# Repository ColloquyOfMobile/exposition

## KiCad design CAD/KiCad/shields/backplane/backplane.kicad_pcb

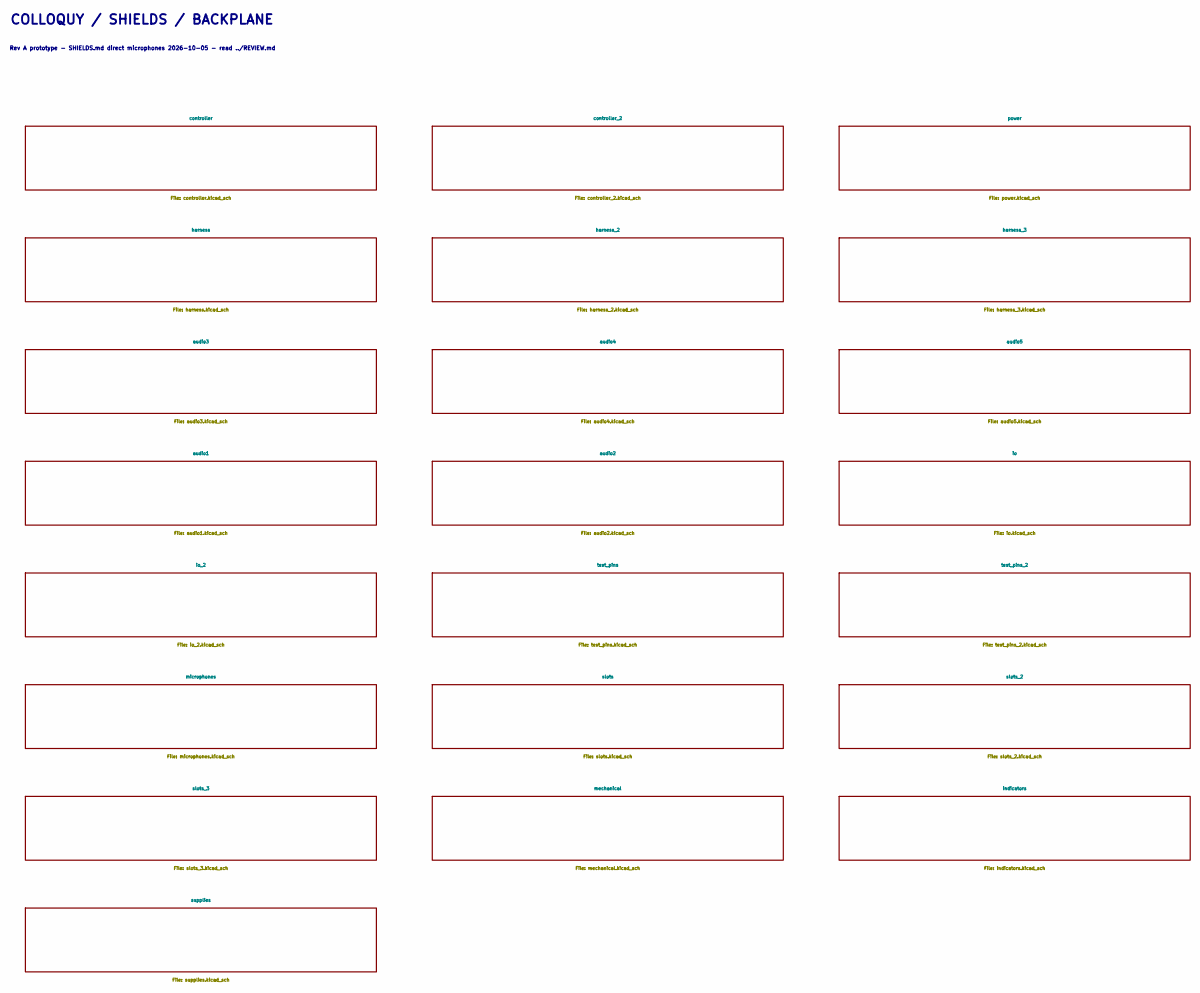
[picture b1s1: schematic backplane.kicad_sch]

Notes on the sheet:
COLLOQUY / SHIELDS / BACKPLANE
Rev A prototype - SHIELDS.md direct microphones 2026-10-05 - read ../REVIEW.md

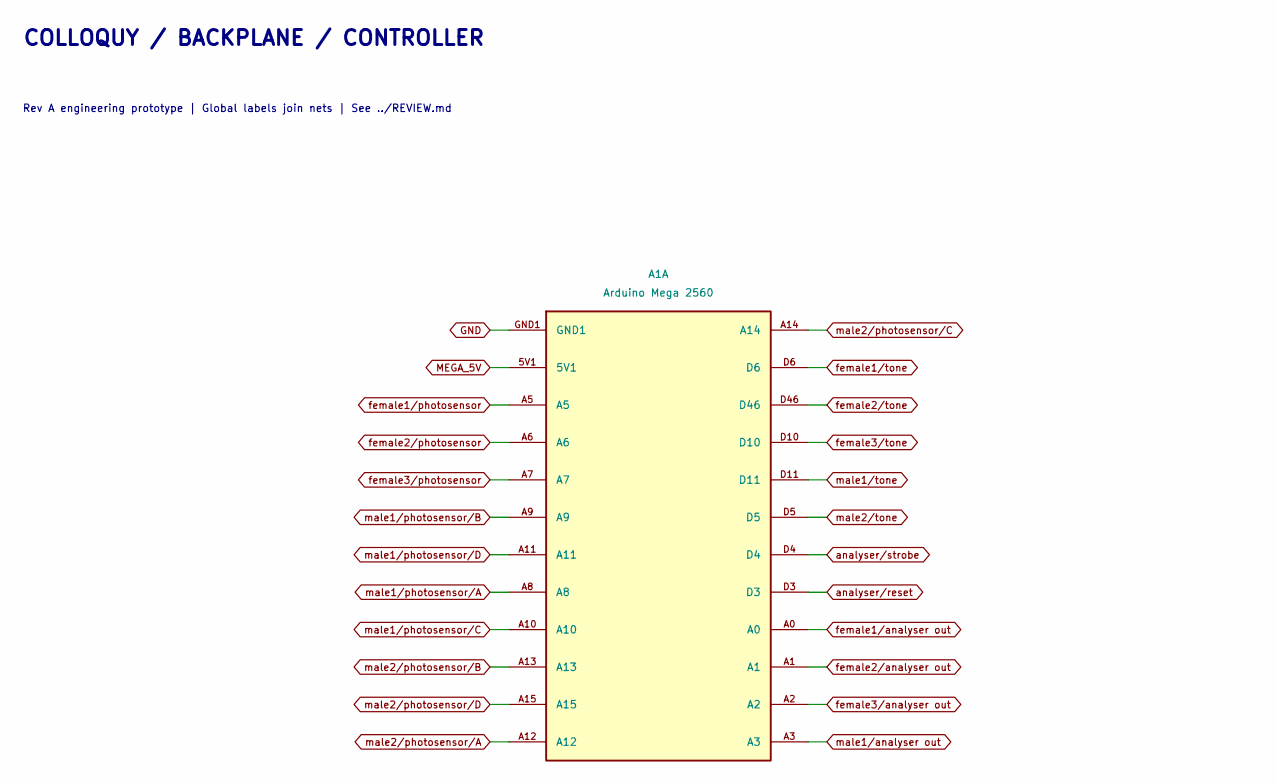
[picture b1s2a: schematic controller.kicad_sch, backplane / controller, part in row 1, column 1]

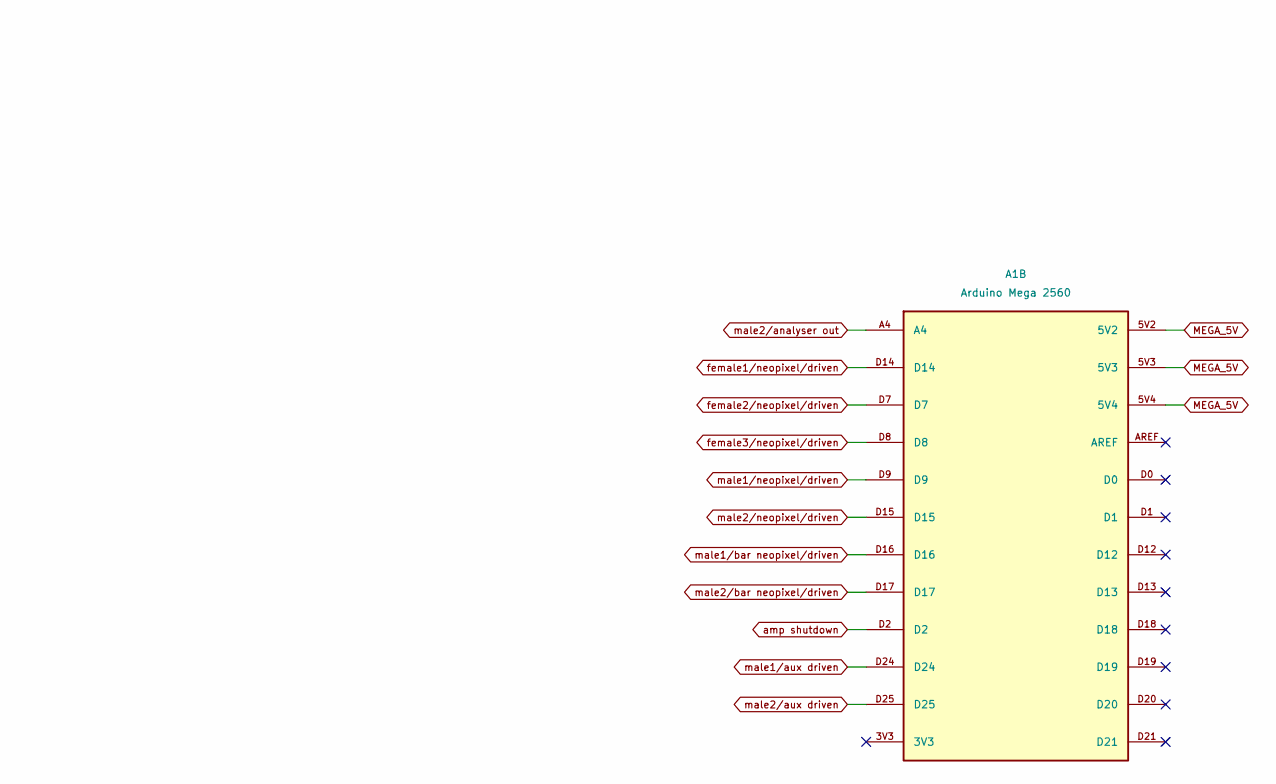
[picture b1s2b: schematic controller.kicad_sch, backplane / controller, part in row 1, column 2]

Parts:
A1: Arduino Mega 2560; Arduino_Mega2560_R3_Shield

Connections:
GND: A1.GND1; also elsewhere on the board
MEGA_5V: A1.5V1, A1.5V2, A1.5V3, A1.5V4; also elsewhere on the board
amp shutdown: A1.D2; also elsewhere on the board
analyser/reset: A1.D3; also elsewhere on the board
analyser/strobe: A1.D4; also elsewhere on the board
female1/analyser out: A1.A0; also elsewhere on the board
female1/neopixel/driven: A1.D14; also elsewhere on the board
female1/photosensor: A1.A5; also elsewhere on the board
female1/tone: A1.D6; also elsewhere on the board
female2/analyser out: A1.A1; also elsewhere on the board
female2/neopixel/driven: A1.D7; also elsewhere on the board
female2/photosensor: A1.A6; also elsewhere on the board
female2/tone: A1.D46; also elsewhere on the board
female3/analyser out: A1.A2; also elsewhere on the board
female3/neopixel/driven: A1.D8; also elsewhere on the board
female3/photosensor: A1.A7; also elsewhere on the board
female3/tone: A1.D10; also elsewhere on the board
male1/analyser out: A1.A3; also elsewhere on the board
male1/aux driven: A1.D24; also elsewhere on the board
male1/bar neopixel/driven: A1.D16; also elsewhere on the board
male1/neopixel/driven: A1.D9; also elsewhere on the board
male1/photosensor/A: A1.A8; also elsewhere on the board
male1/photosensor/B: A1.A9; also elsewhere on the board
male1/photosensor/C: A1.A10; also elsewhere on the board
male1/photosensor/D: A1.A11; also elsewhere on the board
male1/tone: A1.D11; also elsewhere on the board
male2/analyser out: A1.A4; also elsewhere on the board
male2/aux driven: A1.D25; also elsewhere on the board
male2/bar neopixel/driven: A1.D17; also elsewhere on the board
male2/neopixel/driven: A1.D15; also elsewhere on the board
male2/photosensor/A: A1.A12; also elsewhere on the board
male2/photosensor/B: A1.A13; also elsewhere on the board
male2/photosensor/C: A1.A14; also elsewhere on the board
male2/photosensor/D: A1.A15; also elsewhere on the board
male2/tone: A1.D5; also elsewhere on the board

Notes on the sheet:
COLLOQUY / BACKPLANE / CONTROLLER
Rev A engineering prototype | Global labels join nets | See ../REVIEW.md

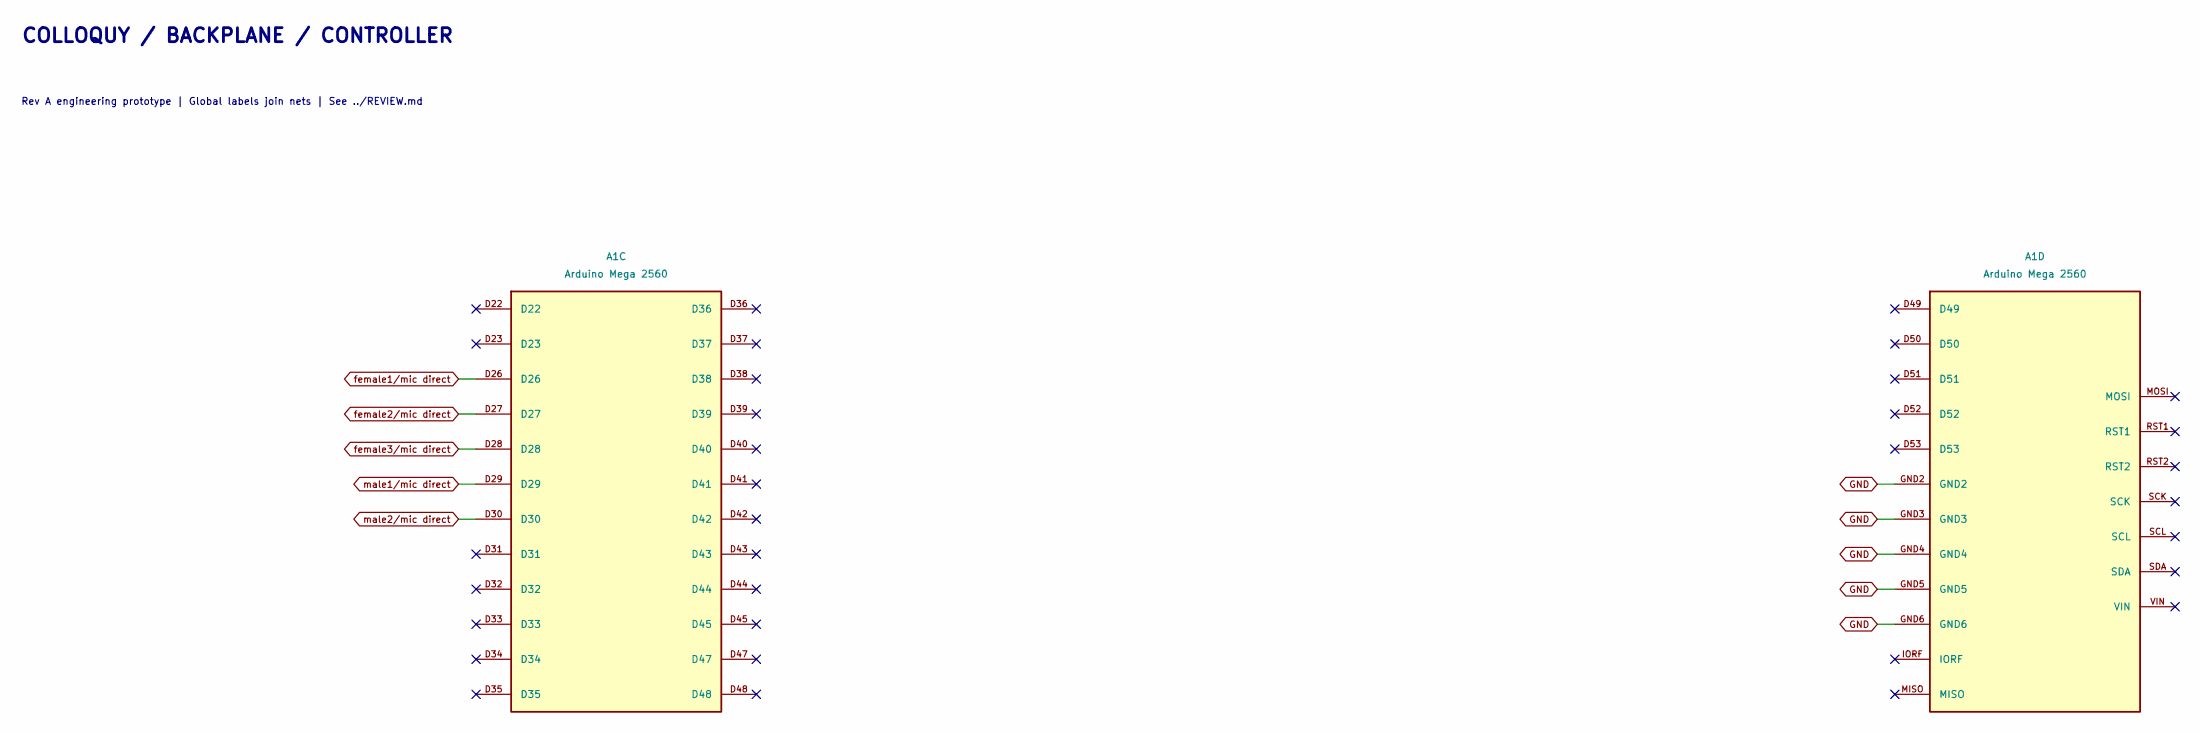
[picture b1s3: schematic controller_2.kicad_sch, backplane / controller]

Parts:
A1: Arduino Mega 2560; Mega_Front_Mirrored

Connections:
GND: A1.GND2, A1.GND3, A1.GND4, A1.GND5, A1.GND6; also elsewhere on the board
female1/mic direct: A1.D26; also elsewhere on the board
female2/mic direct: A1.D27; also elsewhere on the board
female3/mic direct: A1.D28; also elsewhere on the board
male1/mic direct: A1.D29; also elsewhere on the board
male2/mic direct: A1.D30; also elsewhere on the board

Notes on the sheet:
COLLOQUY / BACKPLANE / CONTROLLER
Rev A engineering prototype | Global labels join nets | See ../REVIEW.md

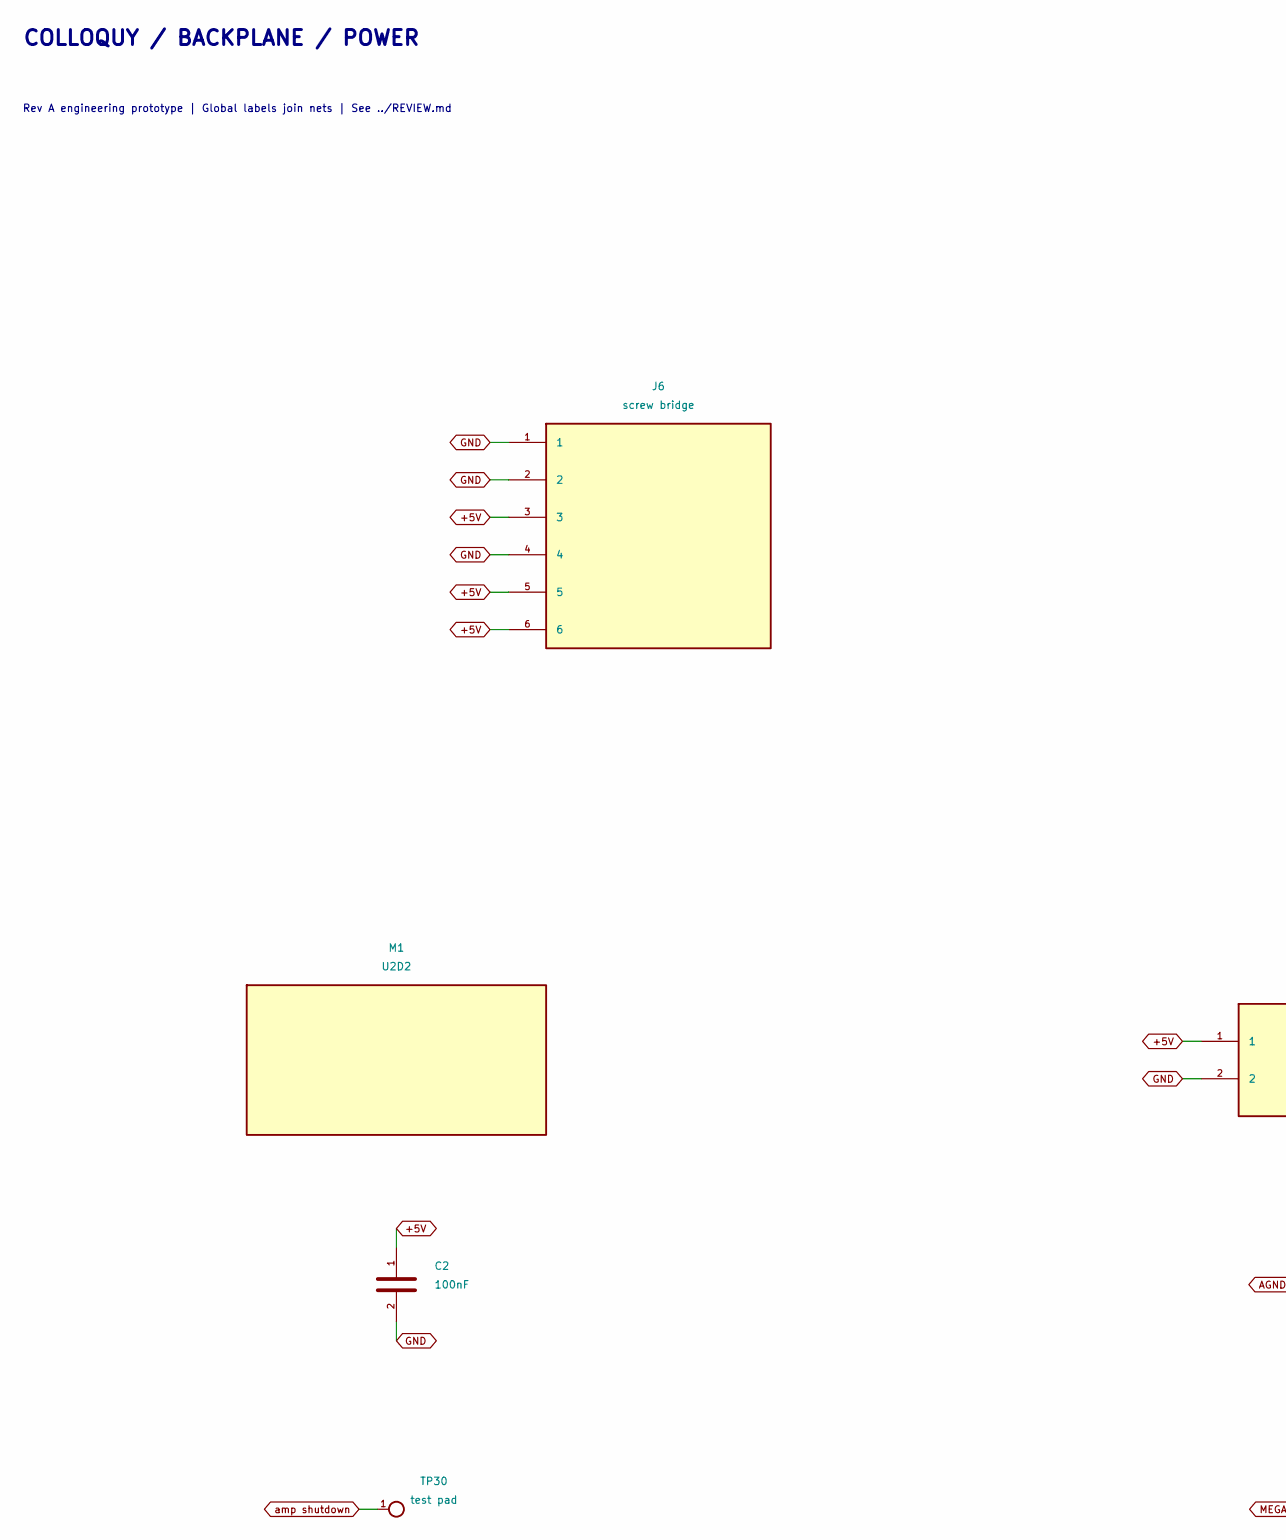
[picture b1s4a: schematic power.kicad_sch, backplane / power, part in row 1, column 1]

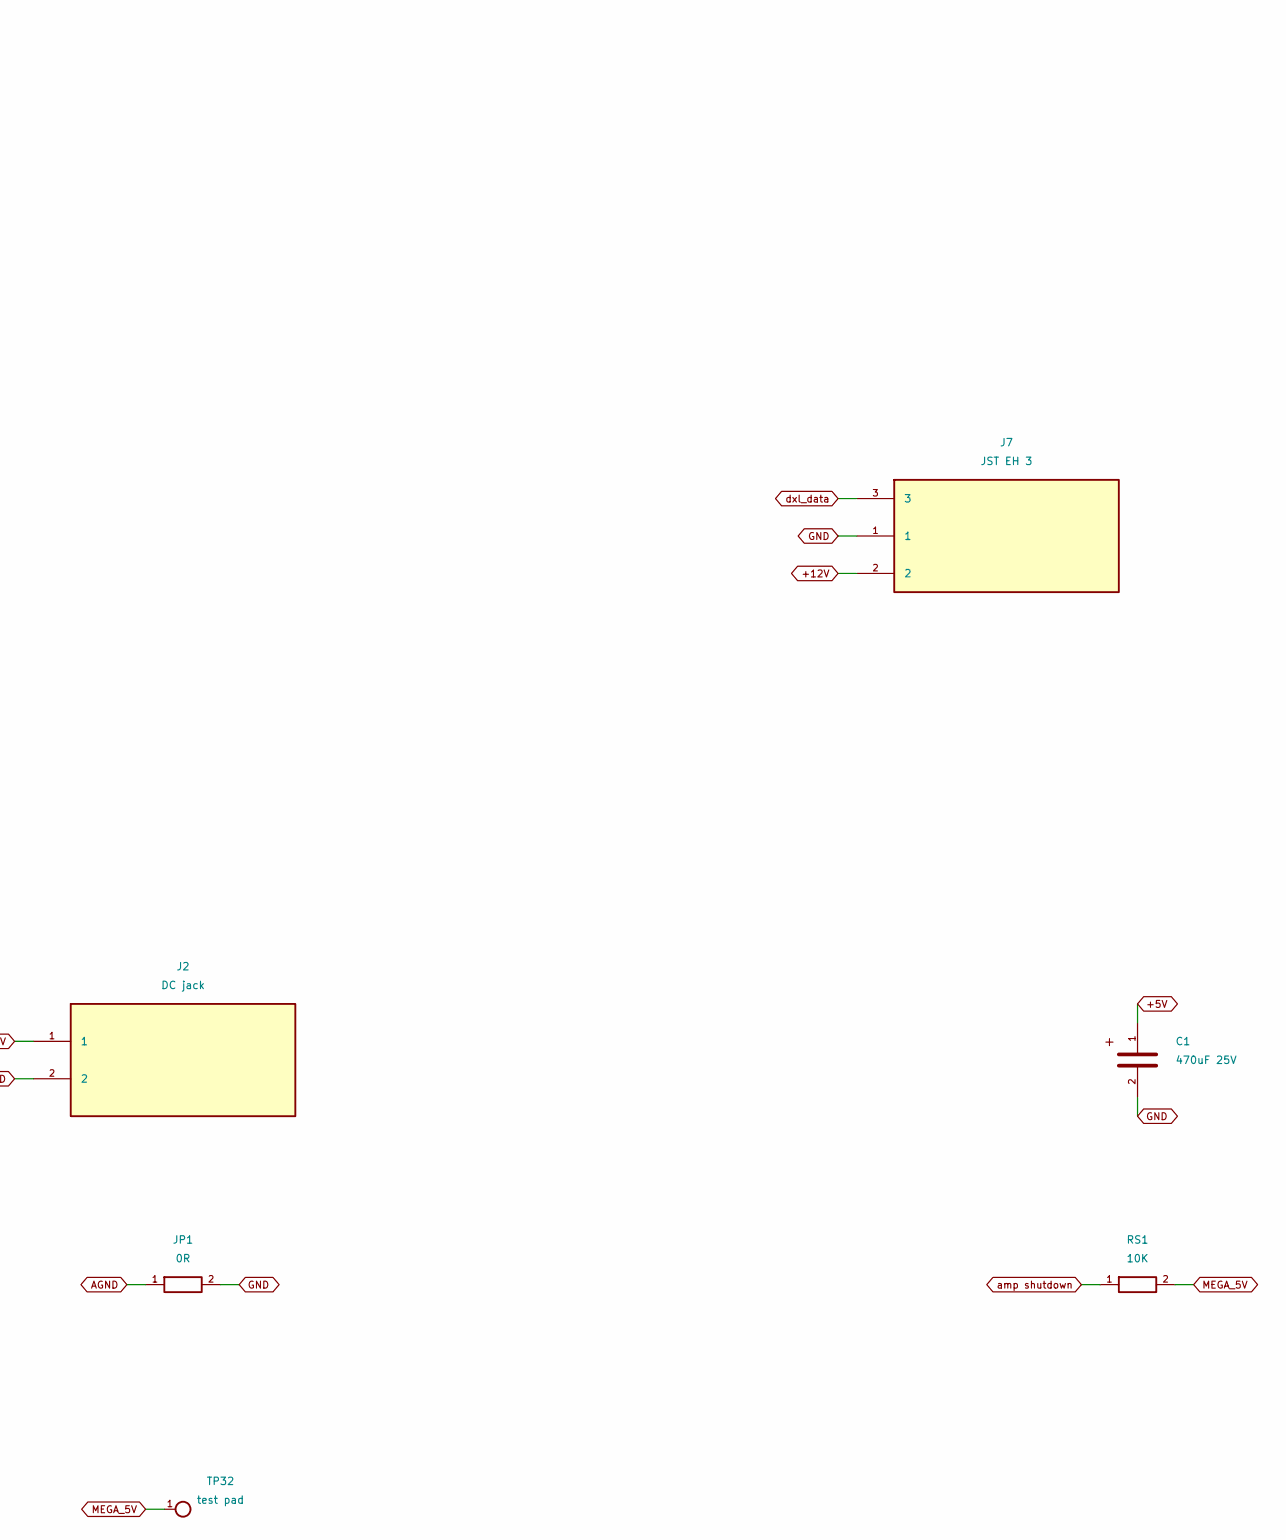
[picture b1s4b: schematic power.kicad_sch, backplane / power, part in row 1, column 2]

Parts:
C1: 470uF 25V; CP_Elec_10x10.5
C2: 100nF; C_0603_1608Metric
J2: DC jack; PJ-082BH_jack_10A
J6: screw bridge; screw_brigde
J7: JST EH 3; JST_EH_B3B-EH-A_1x03_P2.50mm_Vertical
JP1: 0R; R_0805_2012Metric
M1: U2D2; u2d2_mounting
RS1: 10K; R_0603_1608Metric
TP30, TP32: test pad; TestPoint_Pad_D1.5mm

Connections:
+5V: C1.1, C2.1, J2.1, J6.3, J6.5, J6.6; also elsewhere on the board
+12V: J7.2; also elsewhere on the board
AGND: JP1.1; also elsewhere on the board
GND: C1.2, C2.2, J2.2, J6.1, J6.2, J6.4, J7.1, JP1.2; also elsewhere on the board
MEGA_5V: RS1.2, TP32.1; also elsewhere on the board
amp shutdown: RS1.1, TP30.1; also elsewhere on the board
dxl_data: J7.3; also elsewhere on the board

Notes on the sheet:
COLLOQUY / BACKPLANE / POWER
Rev A engineering prototype | Global labels join nets | See ../REVIEW.md

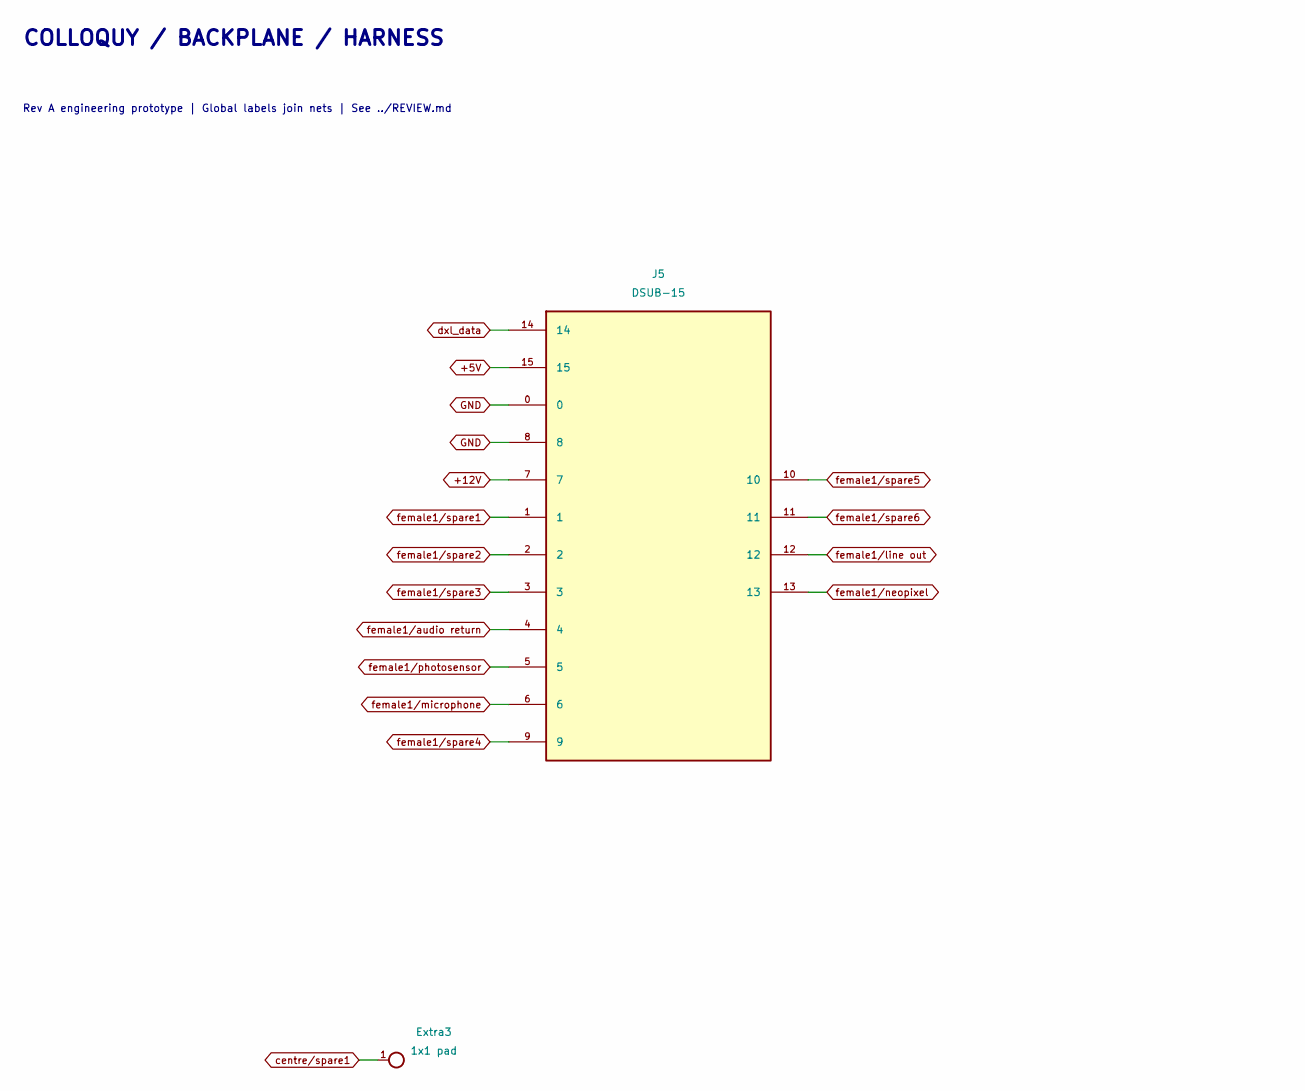
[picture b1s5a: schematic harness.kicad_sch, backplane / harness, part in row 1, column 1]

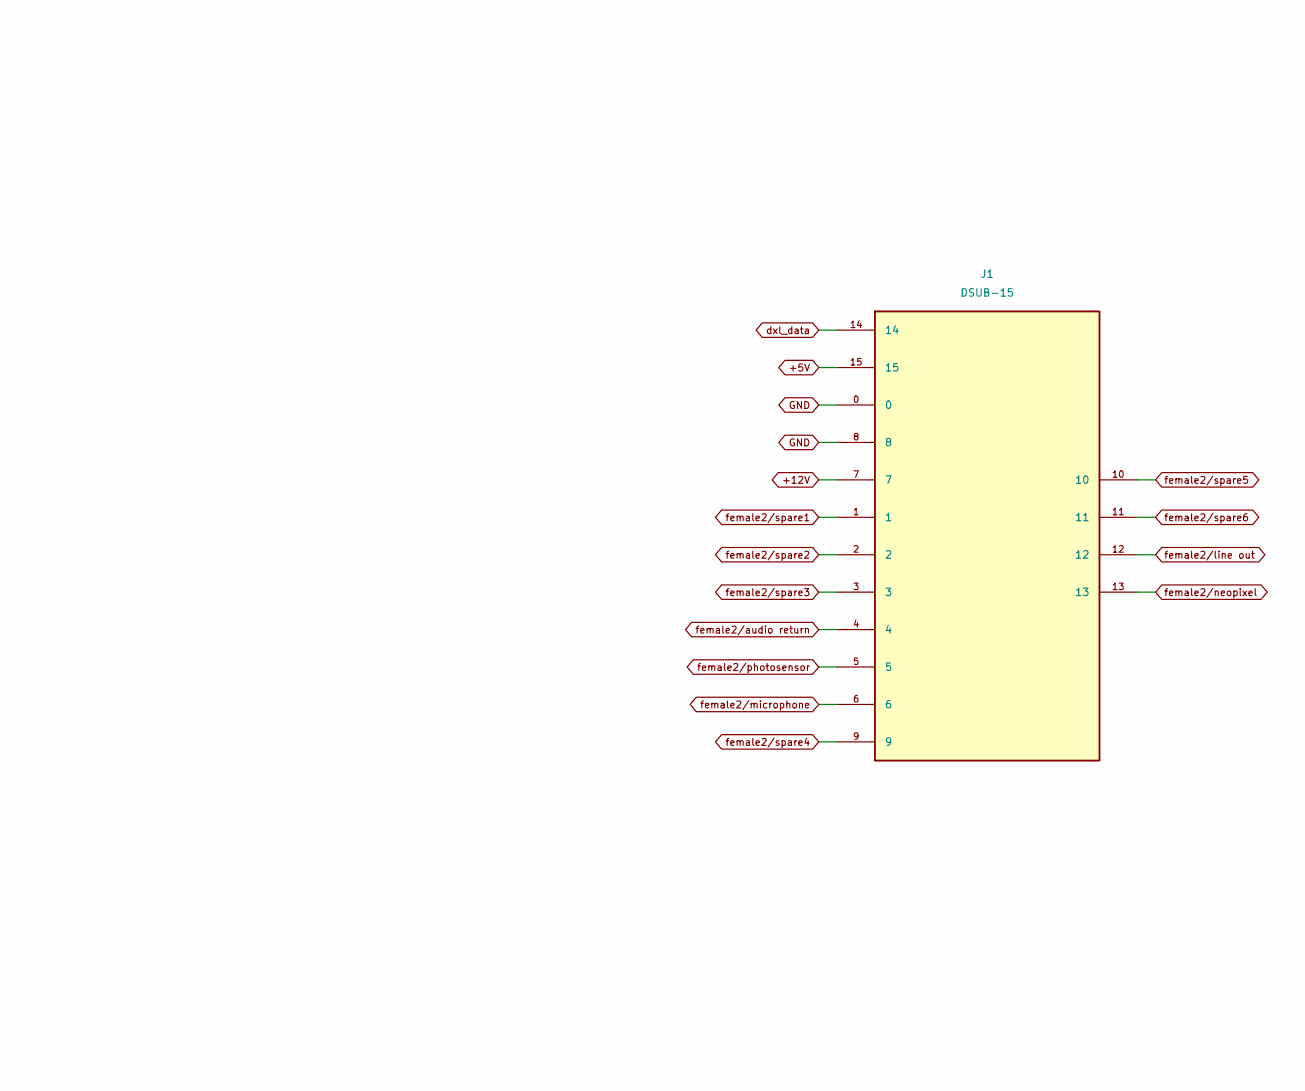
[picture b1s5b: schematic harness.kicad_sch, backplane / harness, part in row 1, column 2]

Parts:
Extra3: 1x1 pad; PinHeader_1x01_P2.54mm_Vertical
J1, J5: DSUB-15; DSUB-15_Pins_Horizontal_P2.77x2.84mm_EdgePinOffset4.94mm_Ho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

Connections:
+5V: J1.15, J5.15; also elsewhere on the board
+12V: J1.7, J5.7; also elsewhere on the board
GND: J1.0, J1.8, J5.0, J5.8; also elsewhere on the board
centre/spare1: Extra3.1; also elsewhere on the board
dxl_data: J1.14, J5.14; also elsewhere on the board
female1/audio return: J5.4; also elsewhere on the board
female1/line out: J5.12; also elsewhere on the board
female1/microphone: J5.6; also elsewhere on the board
female1/neopixel: J5.13; also elsewhere on the board
female1/photosensor: J5.5; also elsewhere on the board
female1/spare1: J5.1; also elsewhere on the board
female1/spare2: J5.2; also elsewhere on the board
female1/spare3: J5.3; also elsewhere on the board
female1/spare4: J5.9; also elsewhere on the board
female1/spare5: J5.10; also elsewhere on the board
female1/spare6: J5.11; also elsewhere on the board
female2/audio return: J1.4; also elsewhere on the board
female2/line out: J1.12; also elsewhere on the board
female2/microphone: J1.6; also elsewhere on the board
female2/neopixel: J1.13; also elsewhere on the board
female2/photosensor: J1.5; also elsewhere on the board
female2/spare1: J1.1; also elsewhere on the board
female2/spare2: J1.2; also elsewhere on the board
female2/spare3: J1.3; also elsewhere on the board
female2/spare4: J1.9; also elsewhere on the board
female2/spare5: J1.10; also elsewhere on the board
female2/spare6: J1.11; also elsewhere on the board

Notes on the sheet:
COLLOQUY / BACKPLANE / HARNESS
Rev A engineering prototype | Global labels join nets | See ../REVIEW.md

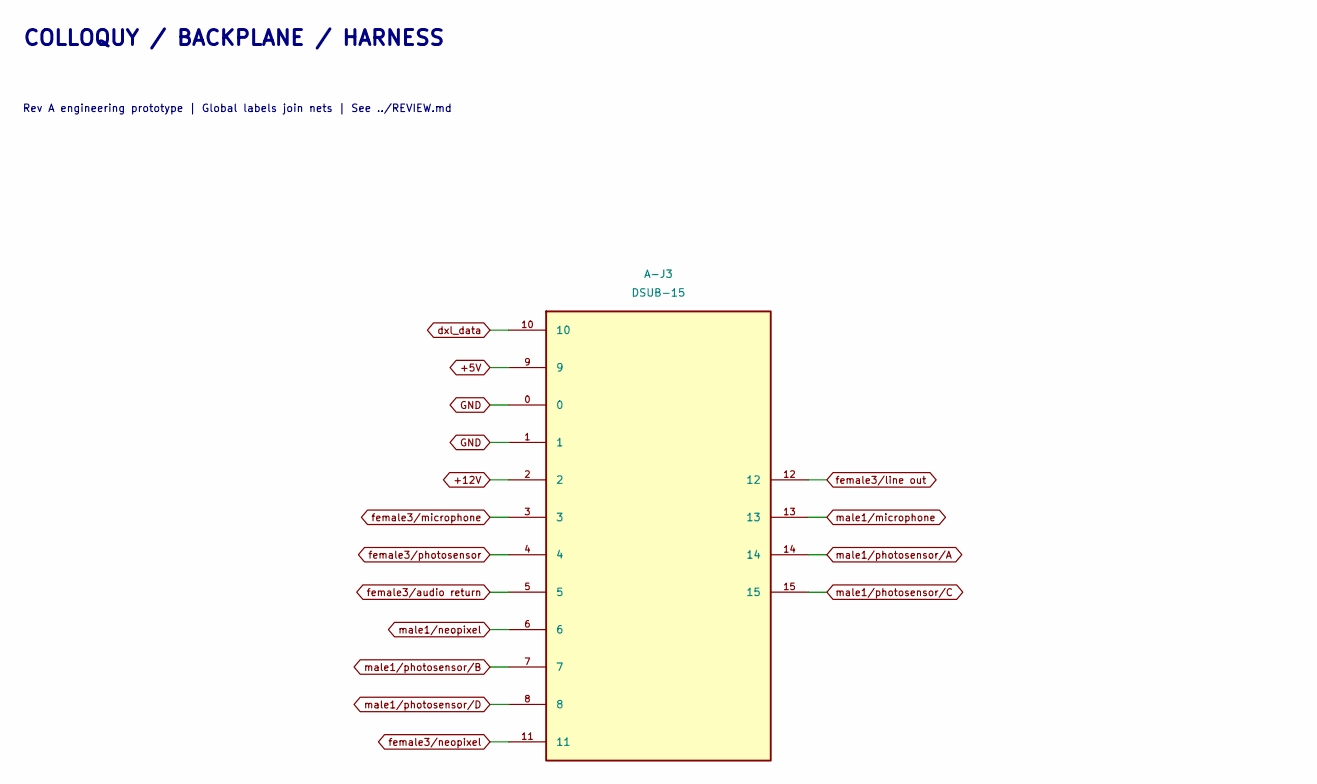
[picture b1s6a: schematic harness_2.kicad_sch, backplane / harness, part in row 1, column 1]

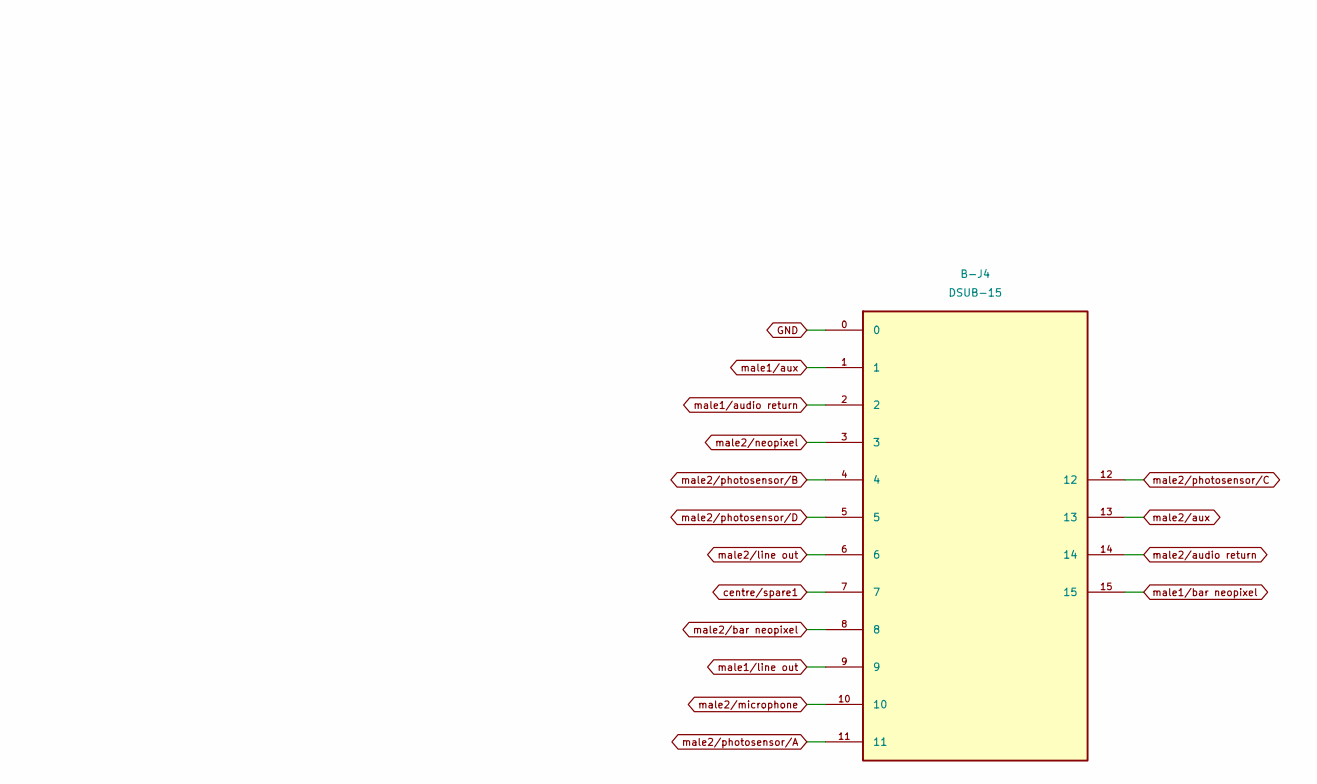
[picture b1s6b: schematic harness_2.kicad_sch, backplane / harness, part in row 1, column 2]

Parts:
A-J3: DSUB-15; DSUB-15_Pins_Horizontal_P2.77x2.84mm_EdgePinOffset4.94mm_Ho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
B-J4: DSUB-15; DSUB-15_Pins_Horizontal_P2.77x2.84mm_EdgePinOffset4.94mm_Ho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

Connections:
+5V: A-J3.9; also elsewhere on the board
+12V: A-J3.2; also elsewhere on the board
GND: A-J3.0, A-J3.1, B-J4.0; also elsewhere on the board
centre/spare1: B-J4.7; also elsewhere on the board
dxl_data: A-J3.10; also elsewhere on the board
female3/audio return: A-J3.5; also elsewhere on the board
female3/line out: A-J3.12; also elsewhere on the board
female3/microphone: A-J3.3; also elsewhere on the board
female3/neopixel: A-J3.11; also elsewhere on the board
female3/photosensor: A-J3.4; also elsewhere on the board
male1/audio return: B-J4.2; also elsewhere on the board
male1/aux: B-J4.1; also elsewhere on the board
male1/bar neopixel: B-J4.15; also elsewhere on the board
male1/line out: B-J4.9; also elsewhere on the board
male1/microphone: A-J3.13; also elsewhere on the board
male1/neopixel: A-J3.6; also elsewhere on the board
male1/photosensor/A: A-J3.14; also elsewhere on the board
male1/photosensor/B: A-J3.7; also elsewhere on the board
male1/photosensor/C: A-J3.15; also elsewhere on the board
male1/photosensor/D: A-J3.8; also elsewhere on the board
male2/audio return: B-J4.14; also elsewhere on the board
male2/aux: B-J4.13; also elsewhere on the board
male2/bar neopixel: B-J4.8; also elsewhere on the board
male2/line out: B-J4.6; also elsewhere on the board
male2/microphone: B-J4.10; also elsewhere on the board
male2/neopixel: B-J4.3; also elsewhere on the board
male2/photosensor/A: B-J4.11; also elsewhere on the board
male2/photosensor/B: B-J4.4; also elsewhere on the board
male2/photosensor/C: B-J4.12; also elsewhere on the board
male2/photosensor/D: B-J4.5; also elsewhere on the board

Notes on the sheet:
COLLOQUY / BACKPLANE / HARNESS
Rev A engineering prototype | Global labels join nets | See ../REVIEW.md

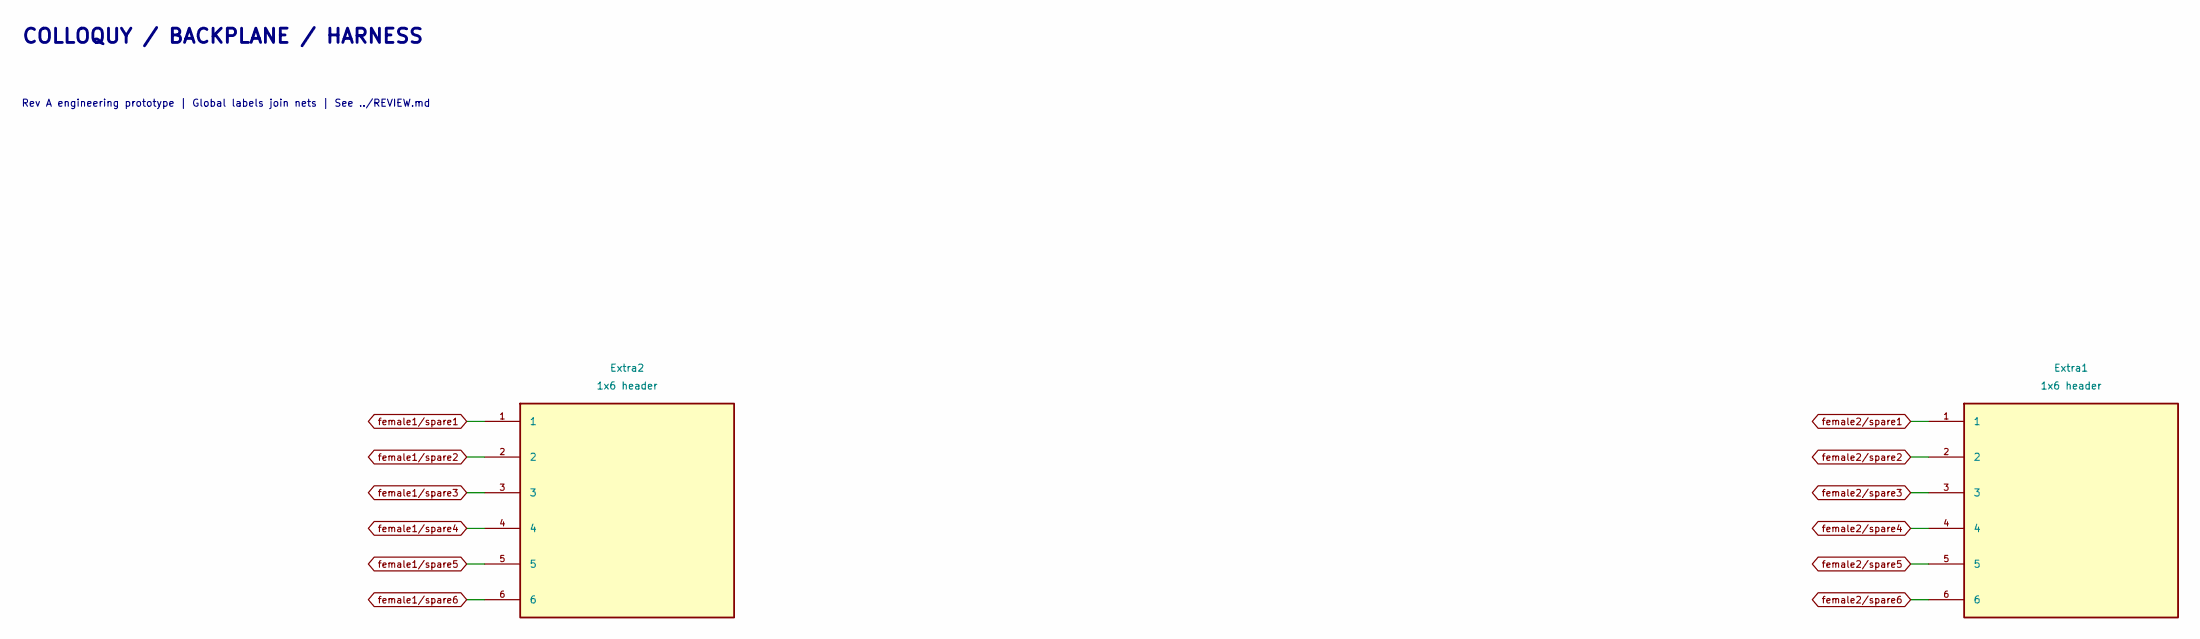
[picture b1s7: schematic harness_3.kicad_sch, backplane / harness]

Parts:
Extra1, Extra2: 1x6 header; PinHeader_1x06_P2.54mm_Vertical

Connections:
female1/spare1: Extra2.1; also elsewhere on the board
female1/spare2: Extra2.2; also elsewhere on the board
female1/spare3: Extra2.3; also elsewhere on the board
female1/spare4: Extra2.4; also elsewhere on the board
female1/spare5: Extra2.5; also elsewhere on the board
female1/spare6: Extra2.6; also elsewhere on the board
female2/spare1: Extra1.1; also elsewhere on the board
female2/spare2: Extra1.2; also elsewhere on the board
female2/spare3: Extra1.3; also elsewhere on the board
female2/spare4: Extra1.4; also elsewhere on the board
female2/spare5: Extra1.5; also elsewhere on the board
female2/spare6: Extra1.6; also elsewhere on the board

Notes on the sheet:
COLLOQUY / BACKPLANE / HARNESS
Rev A engineering prototype | Global labels join nets | See ../REVIEW.md

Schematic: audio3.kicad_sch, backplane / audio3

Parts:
JP4: 0R; R_0805_2012Metric
R303: 100R; R_0805_2012Metric
TP3: test pad; TestPoint_Pad_D1.5mm

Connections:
AGND: JP4.2; also elsewhere on the board
female1/audio return: JP4.1; also elsewhere on the board
female1/filter out: R303.1, TP3.1; also elsewhere on the board
female1/line out: R303.2; also elsewhere on the board

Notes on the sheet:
COLLOQUY / BACKPLANE / AUDIO3
Rev A engineering prototype | Global labels join nets | See ../REVIEW.md

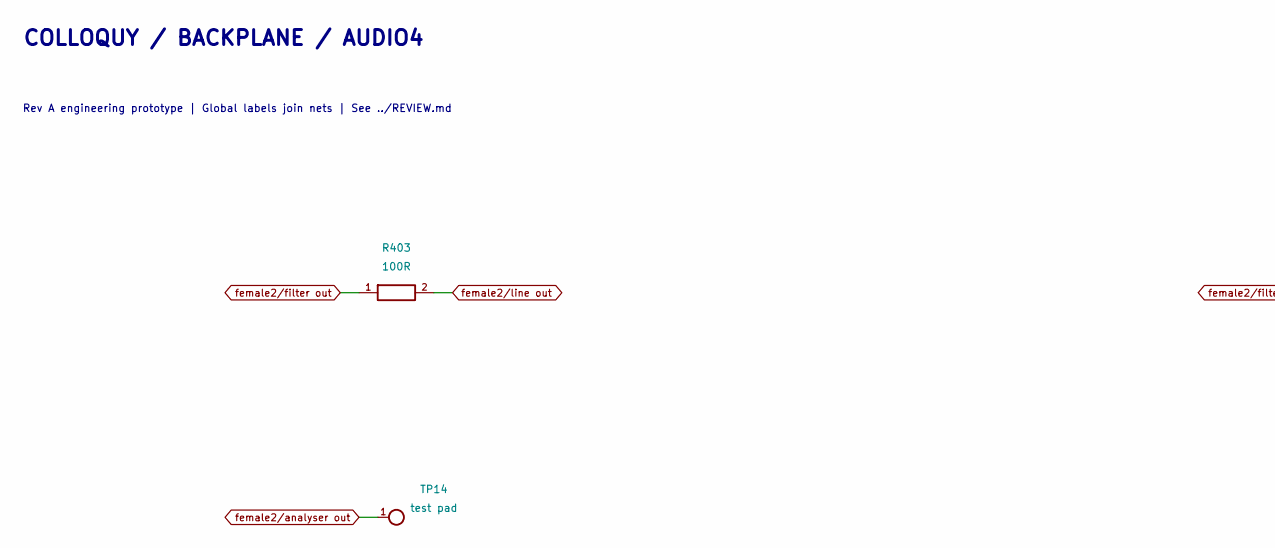
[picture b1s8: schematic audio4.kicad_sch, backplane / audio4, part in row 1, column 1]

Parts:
JP5: 0R; R_0805_2012Metric
R403: 100R; R_0805_2012Metric
TP4, TP14: test pad; TestPoint_Pad_D1.5mm

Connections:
AGND: JP5.2; also elsewhere on the board
female2/audio return: JP5.1; also elsewhere on the board
female2/filter out: R403.1, TP4.1; also elsewhere on the board
female2/line out: R403.2; also elsewhere on the board

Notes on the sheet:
COLLOQUY / BACKPLANE / AUDIO4
Rev A engineering prototype | Global labels join nets | See ../REVIEW.md

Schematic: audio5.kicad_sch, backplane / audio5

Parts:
JP6: 0R; R_0805_2012Metric
R503: 100R; R_0805_2012Metric
TP5: test pad; TestPoint_Pad_D1.5mm

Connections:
AGND: JP6.2; also elsewhere on the board
female3/audio return: JP6.1; also elsewhere on the board
female3/filter out: R503.1, TP5.1; also elsewhere on the board
female3/line out: R503.2; also elsewhere on the board

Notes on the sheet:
COLLOQUY / BACKPLANE / AUDIO5
Rev A engineering prototype | Global labels join nets | See ../REVIEW.md

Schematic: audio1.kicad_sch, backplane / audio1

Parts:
JP2: 0R; R_0805_2012Metric
R103: 100R; R_0805_2012Metric
TP1: test pad; TestPoint_Pad_D1.5mm

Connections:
AGND: JP2.2; also elsewhere on the board
male1/audio return: JP2.1; also elsewhere on the board
male1/filter out: R103.1, TP1.1; also elsewhere on the board
male1/line out: R103.2; also elsewhere on the board

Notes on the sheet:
COLLOQUY / BACKPLANE / AUDIO1
Rev A engineering prototype | Global labels join nets | See ../REVIEW.md

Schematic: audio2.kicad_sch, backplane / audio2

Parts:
JP3: 0R; R_0805_2012Metric
R203: 100R; R_0805_2012Metric
TP2: test pad; TestPoint_Pad_D1.5mm

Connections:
AGND: JP3.2; also elsewhere on the board
male2/audio return: JP3.1; also elsewhere on the board
male2/filter out: R203.1, TP2.1; also elsewhere on the board
male2/line out: R203.2; also elsewhere on the board

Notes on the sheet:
COLLOQUY / BACKPLANE / AUDIO2
Rev A engineering prototype | Global labels join nets | See ../REVIEW.md
